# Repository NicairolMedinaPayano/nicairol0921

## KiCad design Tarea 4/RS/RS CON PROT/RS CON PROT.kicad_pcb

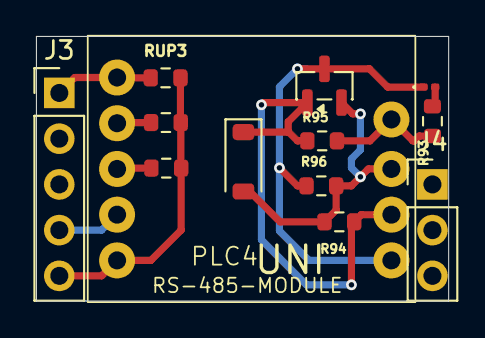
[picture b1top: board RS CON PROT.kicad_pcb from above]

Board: 4 copper layers, 22.9 x 14.7 mm, 13 parts (0 on the bottom side), 10 nets.

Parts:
D712: SM712_SOT23; SOT-23
DL1: LED; LED_0201_0603Metric
DTV1: D_TVS; D_SOD-123
J3: Conn_01x05; PinHeader_1x05_P2.54mm_Vertical
J4: Conn_01x03; PinHeader_1x03_P2.54mm_Vertical
R93, R94, R95, R96: R_US; R_0603_1608Metric
RUP1, RUP2, RUP3: R_US; R_0603_1608Metric
U0: RS485-MODULE-DEVO NU

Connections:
+3.3V: J3.1, RUP1.1, RUP2.1, RUP3.1, U0.1 (VCC)
/RS_mod_pro/RS_485-A: D712.1 (A1), DTV1.1 (A1), J4.9 (Pin_2), R94.2, R95.2, U0.9 (A)
/RS_mod_pro/RS_485-B: D712.2 (A2), DTV1.2 (A2), J4.8 (Pin_1), R94.1, R96.2, U0.8 (B)
/RS_mod_pro/UART_IN: J3.4, RUP2.2, U0.4 (RX)
/RS_mod_pro/UART_OUT: J3.3, RUP1.2, U0.3 (TX)
Earth: J3.2, U0.2 (GND)
unnamed: D712.3 (common), DL1.1 (K), J4.10 (Pin_3), R96.1, U0.10 (RGND)
unnamed: DL1.2 (A), R93.2
unnamed: J3.5, RUP3.2, U0.5 (CON)
unnamed: R93.1, R95.1, U0.7 (VO)

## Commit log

2025-10-10 Delete Ejercicios del capítulo 2 directory
    Sí
2025-10-10 Delete Ejercicios del capítulo 3 directory
    Sí
2025-10-10 Delete Definiciones de comandos.pdf
    Sí
2025-10-10 Delete Resúmenes de los capítulos 1,2,3 y 4 de lógica matemática.pdf
    Sí
2025-10-11 Tarea 1/Trabajos teóricos
2025-10-11 Delete DOC - Plantilla SRS ERS Norma IEEE-830 STD.docx
    Sí
2025-10-11 Tarea 1
    Tarea 1: Trabajos teóricos de Word
2025-10-11 Tarea 1
2025-10-11 Delete Tarea 1. Trabajos teóricos de Word directory
    Sí
2025-10-11 Tarea 2. Video, Ensamblajes FreeCAD y Solid Edge
